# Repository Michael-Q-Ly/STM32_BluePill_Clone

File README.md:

# KiCad V6 STM32 Blue Pill Hardware Design

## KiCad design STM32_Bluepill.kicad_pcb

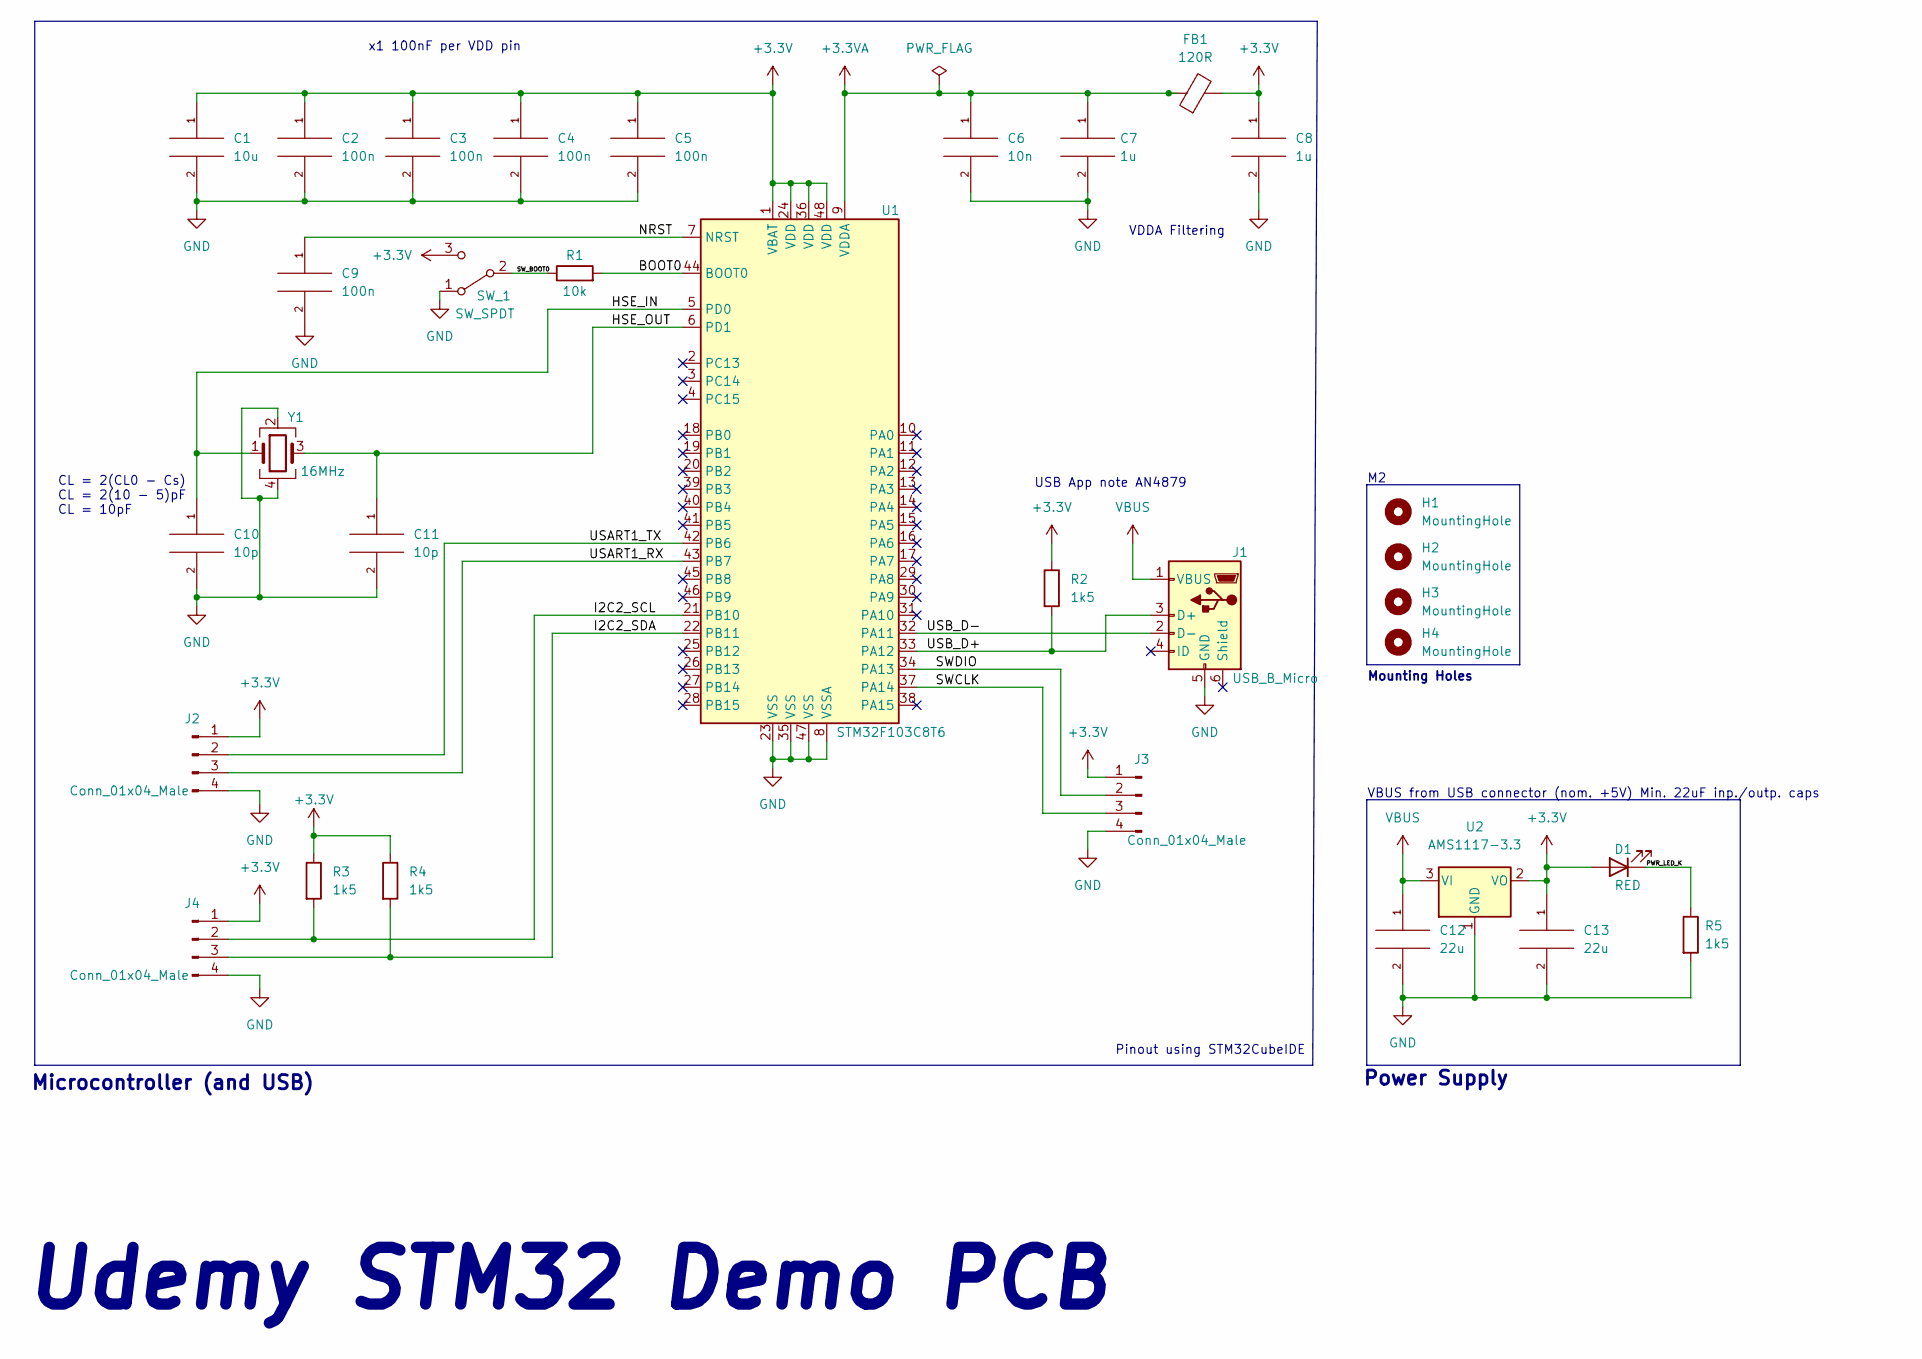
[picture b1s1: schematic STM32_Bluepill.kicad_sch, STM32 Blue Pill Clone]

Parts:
C1: 10u; C_0603_1608Metric
C2, C3, C4, C5, C9: 100n; C_0402_1005Metric
C6: 10n; C_0402_1005Metric
C7, C8: 1u; C_0402_1005Metric
C10, C11: 10p; C_0402_1005Metric
C12, C13: 22u; C_0805_2012Metric
D1: RED; LED_0603_1608Metric
FB1: 120R; L_0603_1608Metric
H1, H2, H3, H4: MountingHole; MountingHole_2.2mm_M2
J1: USB_B_Micro; USB_Micro-B_Wuerth_629105150521
J2, J3, J4: Conn_01x04_Male; PinHeader_1x04_P2.54mm_Vertical
R1: 10k; R_0402_1005Metric
R2, R3, R4, R5: 1k5; R_0402_1005Metric
SW_1: SW_SPDT; SW_SPDT_PCM12
U1: STM32F103C8T6; LQFP-48_7x7mm_P0.5mm
U2: AMS1117-3.3; SOT-223-3_TabPin2
Y1: 16MHz; Crystal_SMD_3225-4Pin_3.2x2.5mm

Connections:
+3.3V: C1.1, C2.1, C3.1, C4.1, C5.1, C8.1, C13.1, D1.2 (A), FB1.2, J2.1, J3.1, J4.1, R2.1, R3.1, R4.1, SW_1.3 (C), U1.1 (VBAT), U1.24 (VDD), U1.36 (VDD), U1.48 (VDD), U2.2 (VO)
+3.3VA: C6.1, C7.1, FB1.1, U1.9 (VDDA)
/BOOT0: R1.2, U1.44 (BOOT0)
/HSE_IN: C10.1, U1.5 (PD0), Y1.1
/HSE_OUT: C11.1, U1.6 (PD1), Y1.3
/I2C2_SCL: J4.2, R3.2, U1.21 (PB10)
/I2C2_SDA: J4.3, R4.2, U1.22 (PB11)
/NRST: C9.1, U1.7 (NRST)
/PWR_LED_K: D1.1 (K), R5.1
/SWCLK: J3.3, U1.37 (PA14)
/SWDIO: J3.2, U1.34 (PA13)
/SW_BOOT0: R1.1, SW_1.2 (B)
/USART1_RX: J2.3, U1.43 (PB7)
/USART1_TX: J2.2, U1.42 (PB6)
/USB_D+: J1.3 (D+), R2.2, U1.33 (PA12)
/USB_D-: J1.2 (D-), U1.32 (PA11)
GND: C1.2, C2.2, C3.2, C4.2, C5.2, C6.2, C7.2, C8.2, C9.2, C10.2, C11.2, C12.2, C13.2, J1.5 (GND), J2.4, J3.4, J4.4, R5.2, SW_1.1 (A), U1.8 (VSSA), U1.23 (VSS), U1.35 (VSS), U1.47 (VSS), U2.1 (GND), Y1.2, Y1.4
VBUS: C12.1, J1.1 (VBUS), U2.3 (VI)

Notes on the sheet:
Microcontroller (and USB)
Pinout using STM32CubeIDE
CL = 2(CL0 - Cs) CL = 2(10 - 5)pF CL = 10pF
Mounting Holes
x1 100nF per VDD pin
USB App note AN4879
VDDA Filtering
Udemy STM32 Demo PCB
VBUS from USB connector (nom. +5V) Min. 22uF inp./outp. caps
Power Supply

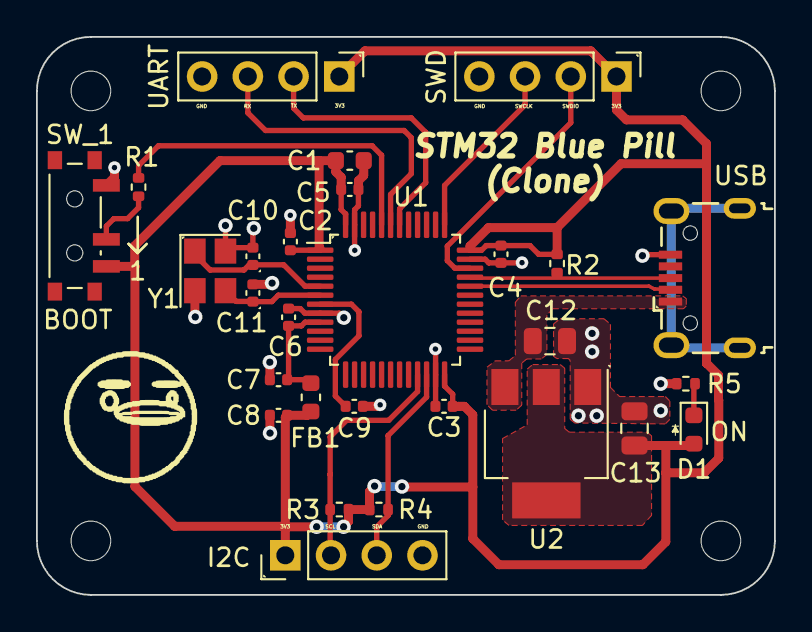
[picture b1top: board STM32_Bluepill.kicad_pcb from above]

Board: 2 copper layers, 41.0 x 31.0 mm, 33 parts (0 on the bottom side), 18 nets.

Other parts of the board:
Ducky: LOGO

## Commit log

2022-12-10 Create new KiCad project
2022-12-10 Schematic: Add MCU and decoupling caps / bulk caps
    - Also add VDD and VDDA
2022-12-10 Schematic: Add Configuration pins NRST and BOOT0
    - Add a switch for BOOT0 to allow it to be programmed
    - NRST should already have an internal pullup
2022-12-10 Schematic: Add Pin-out net names
    - HSE_IN, HSE_OUT
    - USB_D-, USB_D+ (Same name & -/+ signifies differential pair)
    - SWDIO
    - SWCLK
2022-12-10 Schematic: Add power supply and connectors
    - 3.3V Linear regulator with PWR_LED
    - Connectors for USART and I2C
    - Many resistors are 1.5k to save on the BOM
2022-12-10 Schematic: Fix wrong cap value in VDDA Filtering from 10nF to 1uF
2022-12-10 Schematic: Change LED name to RED
2022-12-10 Schematic: Add USB B Micro and STM USB app note
    - Use USB App note from STM to get what pullup resistor value to
    use on the USB_D+ line
2022-12-10 Schematic: Add crystal circuitry
    - STM has a crystal design guide - Application Note # AN2867
    - 10 pF crystal with a stray capacitance of 3-5 pF gives us
    around 5pF, multiplying by 2 gives 10pF caps attached to the
    crystal
    - Calculating these caps also found in the datasheet
2022-12-10 Schematic: Annotate and add notes and run ERC; also add PWR_FLAG
2022-12-10 Schematic: Assign footprints to schematic symbols
2022-12-11 Layout: Specify Board Settings from OSHPARK
2022-12-11 Layout: Add Rat's Nest and edit page info
2022-12-15 Begin routing by importing rat's nest
2022-12-15 Layout: Layout decoupling caps, filtering, and oscillator
2022-12-17 Layout: Place USB and SWD (Serial Wirte Debugger)
2022-12-17 Layout: Change switch's footprint to be a smaller SMD one
2022-12-17 Layout: Add 3D model/stp file of USB connector
2022-12-17 Layout: replace 3D model with new USB connector
    - You can do this by looking up the part number in the schematic
    and then going to a site such as Digi-Key and downloading its
    3D CAD model
    - Offset y- and z- axes by 1.000 mm to get the pads to align
2022-12-17 Schematic: Rename SW_BOOT1 to SW_1 and add net label called SW_BOOT1
2022-12-17 Layout: Place switch and connectors
2022-12-17 Layout: Place power supplies and bulk cap
2022-12-17 Schematic: Add M2 mounting holes
2022-12-17 Layout: Add mounting holes and edge cuts
2022-12-17 Routing: Do ground pour
2022-12-17 Routing: Route decoupling caps first then XTL HSE_IN/OUT
2022-12-17 Schematic/Layout: Rename SW_BOOT1 to SW_BOOT0 for net name
2022-12-17 Routing: Route signals
2022-12-18 Routing: Route PWR and GND
    - Use 0.5 mm tracks for these
    - Create fills for grouped GND or PWR
    - Move some things around to accommodate
2022-12-18 Silkscreen: Put markings to indicate pin 1 on components + run DRC
2022-12-18 Add duck image for silkscreen
2022-12-18 Silkscreen: Add custom duck image and board details on back of board
2022-12-18 Routing: Fix a 0.3 mm 3V3 trace to a 0.5 mm trace
2022-12-18 Manufacturing: Add BOM, gerber, and drill files & archive them
2022-12-18 Routing: Turn R5 to make routing easier
2022-12-18 Manufacturing: Regenerate position, drill, and gerber files after R5 rotation
